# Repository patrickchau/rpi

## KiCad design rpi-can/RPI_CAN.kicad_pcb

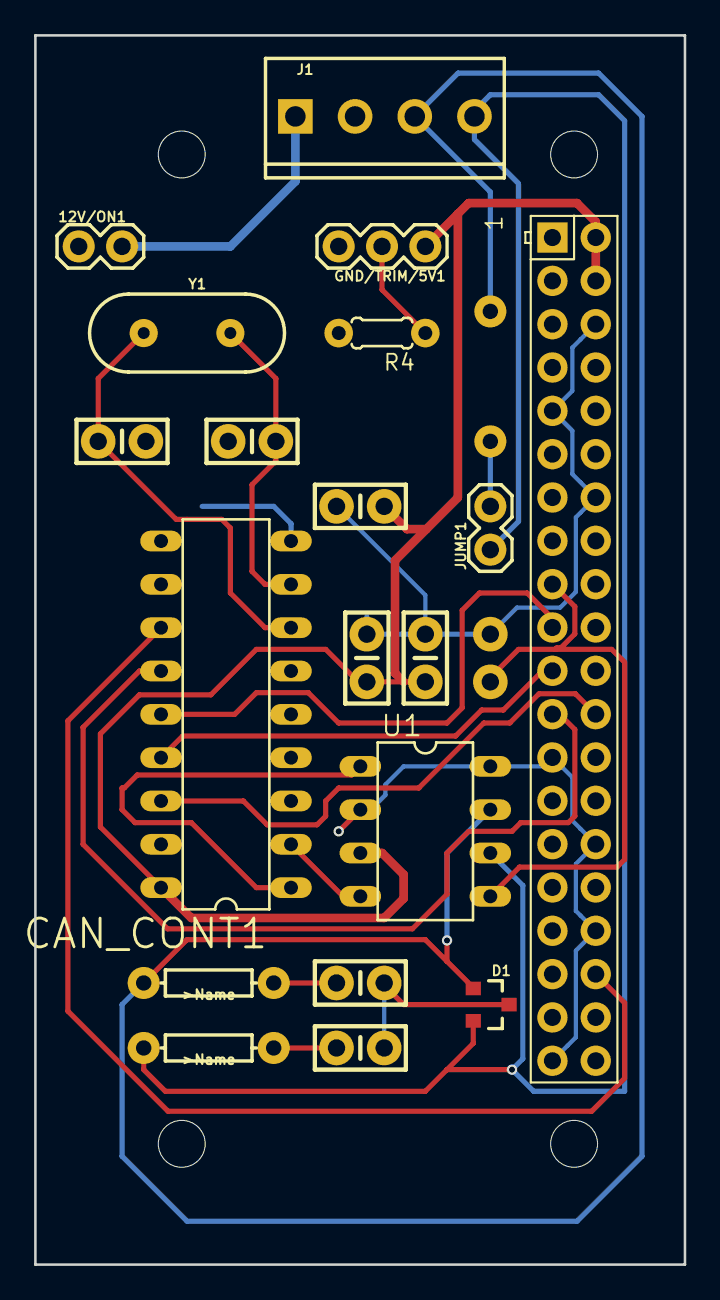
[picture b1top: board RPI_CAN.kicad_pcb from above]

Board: 2 copper layers, 38.1 x 72.1 mm, 21 parts (0 on the bottom side), 19 nets.

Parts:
12V/ON1: 1; 1X02
C1, C4: 22pF; CAP-PTH-SMALL-KIT
C2, C3: 560pF; CAP-PTH-SMALL-KIT
C5, C6, C7, C8: 0.1uF; CAP-PTH-SMALL-KIT
CAN_CONT1: MCP2515P; DIL18
D1: PESD1CAN; SOT23-3
GND/TRIM/5V1: 1; 1X03
J1: 1; SCREWTERMINAL-3.5MM-4
JUMP1: 2; 1X02
R1, R2: 100; AXIAL-0.3EZ
R3: 120; AXIAL-0.3
R4: 1472ohms; 0204_5
U1: MCP2562DIL08_2; DIL08
U$1: RPI-ZERO; RASP_PI_ZERO_BOARD_FULL
Y1: 16MHz; HC49US

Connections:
3V3: C7.2, U1.5, U$1.1, U$1.17
5V: C5.1, C6.2, C8.1, CAN_CONT1.18, GND/TRIM/5V1.1, U1.3, U$1.2, U$1.4
/12V: 12V/ON1.2, J1.1
/CANH: D1.1, J1.3, R1.P$2, R3.P$1, U1.7
/CANL: D1.2, J1.4, JUMP1.1, R2.P$2, U1.6
/CANRXD: CAN_CONT1.2, U1.4
/CANTXD: CAN_CONT1.1, U1.1
/CAN_C_CS: CAN_CONT1.16, U$1.24
/CAN_C_INT: CAN_CONT1.12, U$1.36
/CAN_C_SCK: CAN_CONT1.13, U$1.23
/CAN_C_SI: CAN_CONT1.14, U$1.19
/CAN_C_SO: CAN_CONT1.15, U$1.21
/TRIM: GND/TRIM/5V1.2, R4.1
GND: C1.1, C2.2, C3.2, C4.1, C5.2, C6.1, C7.1, C8.2, CAN_CONT1.9, D1.3, GND/TRIM/5V1.3, J1.2, R4.2, U1.2, U1.8, U$1.6, U$1.9, U$1.14, U$1.20, U$1.25, U$1.30, U$1.34, U$1.39
unnamed: C1.2, CAN_CONT1.8, Y1.2
unnamed: C2.1, R1.P$1
unnamed: C3.1, R2.P$1
unnamed: C4.2, CAN_CONT1.7, Y1.1
unnamed: JUMP1.2, R3.P$2

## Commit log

2020-06-28 initial upload
2020-06-28 added eagle files
